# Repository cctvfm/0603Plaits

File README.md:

# 0603Plaits
a 603 Conversion of the Mutable Instruments Module Plaints
Confirmed working.
# TODO
Fix Eagle files. The .sch and .brd are inconsistent due to a crash after finalizing design

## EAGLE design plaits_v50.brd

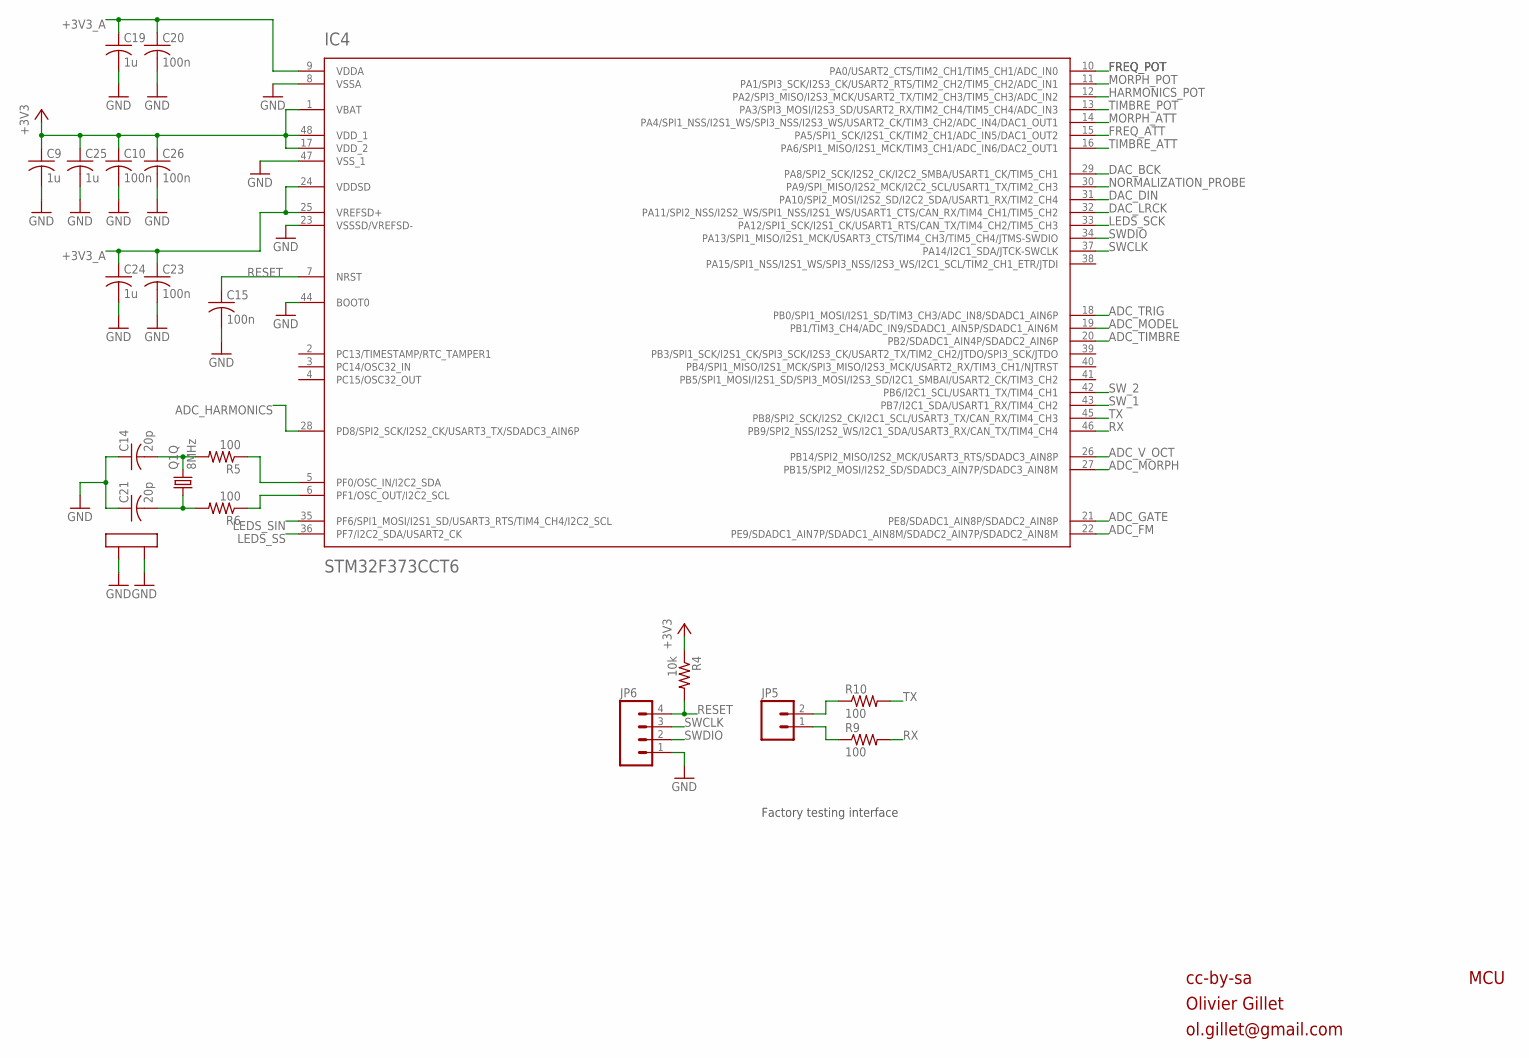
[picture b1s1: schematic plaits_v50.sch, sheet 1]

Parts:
C9, C19, C24, C25: 1u; C0603K
C10, C15, C20, C23, C26: 100n; C0603K
C14, C21: 20p; C0603K
IC4: STM32F373CCT6; LQFP48
JP5: M02PTH; 1X02
JP6: M04PTH; 1X04
Q1: 8MHz; CTS406
R4: 10k; R0603
R5, R6, R9, R10: 100; R0603

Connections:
+3V3: C9.1, C10.1, C25.1, C26.1, IC4.1 (VBAT), IC4.17 (VDD_2), IC4.48 (VDD_1), R4.1; also elsewhere on the board
+3V3_A: C19.1, C20.1, C23.1, C24.1, IC4.9 (VDDA), IC4.24 (VDDSD), IC4.25 (VREFSD+); also elsewhere on the board
ADC_FM: IC4.22 (PE9/SDADC1_AIN7P/SDADC1_AIN8M/SDADC2_AI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); also elsewhere on the board
ADC_GATE: IC4.21 (PE8/SDADC1_AIN8P/SDADC2_AIN8P); also elsewhere on the board
ADC_HARMONICS: IC4.28 (PD8/SPI2_SCK/I2S2_CK/USART3_TX/SDADC3_A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); also elsewhere on the board
ADC_MODEL: IC4.19 (PB1/TIM3_CH4/ADC_IN9/SDADC1_AIN5P/SDADC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); also elsewhere on the board
ADC_MORPH: IC4.27 (PB15/SPI2_MOSI/I2S2_SD/SDADC3_AIN7P/SDA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); also elsewhere on the board
ADC_TIMBRE: IC4.20 (PB2/SDADC1_AIN4P/SDADC2_AIN6P); also elsewhere on the board
ADC_TRIG: IC4.18 (PB0/SPI1_MOSI/I2S1_SD/TIM3_CH3/ADC_IN8/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); also elsewhere on the board
ADC_V_OCT: IC4.26 (PB14/SPI2_MISO/I2S2_MCK/USART3_RTS/SDAD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); also elsewhere on the board
DAC_BCK: IC4.29 (PA8/SPI2_SCK/I2S2_CK/I2C2_SMBA/USART1_C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); also elsewhere on the board
DAC_DIN: IC4.31 (PA10/SPI2_MOSI/I2S2_SD/I2C2_SDA/USART1_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); also elsewhere on the board
DAC_LRCK: IC4.32 (PA11/SPI2_NSS/I2S2_WS/SPI1_NSS/I2S1_WS/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); also elsewhere on the board
FREQ_ATT: IC4.15 (PA5/SPI1_SCK/I2S1_CK/TIM2_CH1/ADC_IN5/D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); also elsewhere on the board
FREQ_POT: IC4.10 (PA0/USART2_CTS/TIM2_CH1/TIM5_CH1/ADC_IN0); also elsewhere on the board
GND: C9.2, C10.2, C14.1, C15.2, C19.2, C20.2, C21.1, C23.2, C24.2, C25.2, C26.2, IC4.8 (VSSA), IC4.23 (VSSSD/VREFSD-), IC4.44 (BOOT0), IC4.47 (VSS_1), JP6.1, Q1.2 (LID1), Q1.4 (LID2); also elsewhere on the board
HARMONICS_POT: IC4.12 (PA2/SPI3_MISO/I2S3_MCK/USART2_TX/TIM2_C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); also elsewhere on the board
LEDS_SCK: IC4.33 (PA12/SPI1_SCK/I2S1_CK/USART1_RTS/CAN_TX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); also elsewhere on the board
LEDS_SIN: IC4.35 (PF6/SPI1_MOSI/I2S1_SD/USART3_RTS/TIM4_C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); also elsewhere on the board
LEDS_SS: IC4.36 (PF7/I2C2_SDA/USART2_CK); also elsewhere on the board
MORPH_ATT: IC4.14 (PA4/SPI1_NSS/I2S1_WS/SPI3_NSS/I2S3_WS/U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); also elsewhere on the board
MORPH_POT: IC4.11 (PA1/SPI3_SCK/I2S3_CK/USART2_RTS/TIM2_CH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); also elsewhere on the board
unnamed: IC4.5 (PF0/OSC_IN/I2C2_SDA), R5.1
unnamed: IC4.6 (PF1/OSC_OUT/I2C2_SCL), R6.1
unnamed: C14.2, Q1.3 (2), R5.2
unnamed: JP5.2, R10.1
unnamed: C21.2, Q1.1, R6.2
unnamed: JP5.1, R9.1
NORMALIZATION_PROBE: IC4.30 (PA9/SPI_MISO/I2S2_MCK/I2C2_SCL/USART1_T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); also elsewhere on the board
RESET: C15.1, IC4.7 (NRST), JP6.4, R4.2
RX: IC4.46 (PB9/SPI2_NSS/I2S2_WS/I2C1_SDA/USART3_RX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), R9.2
SWCLK: IC4.37 (PA14/I2C1_SDA/JTCK-SWCLK), JP6.3
SWDIO: IC4.34 (PA13/SPI1_MISO/I2S1_MCK/USART3_CTS/TIM4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), JP6.2
SW_1: IC4.43 (PB7/I2C1_SDA/USART1_RX/TIM4_CH2); also elsewhere on the board
SW_2: IC4.42 (PB6/I2C1_SCL/USART1_TX/TIM4_CH1); also elsewhere on the board
TIMBRE_ATT: IC4.16 (PA6/SPI1_MISO/I2S1_MCK/TIM3_CH1/ADC_IN6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); also elsewhere on the board
TIMBRE_POT: IC4.13 (PA3/SPI3_MOSI/I2S3_SD/USART2_RX/TIM2_CH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); also elsewhere on the board
TX: IC4.45 (PB8/SPI2_SCK/I2S2_CK/I2C1_SCL/USART3_TX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), R10.2

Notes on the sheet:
cc-by-sa
Olivier Gillet
ol.gillet@gmail.com
MCU
Factory testing interface

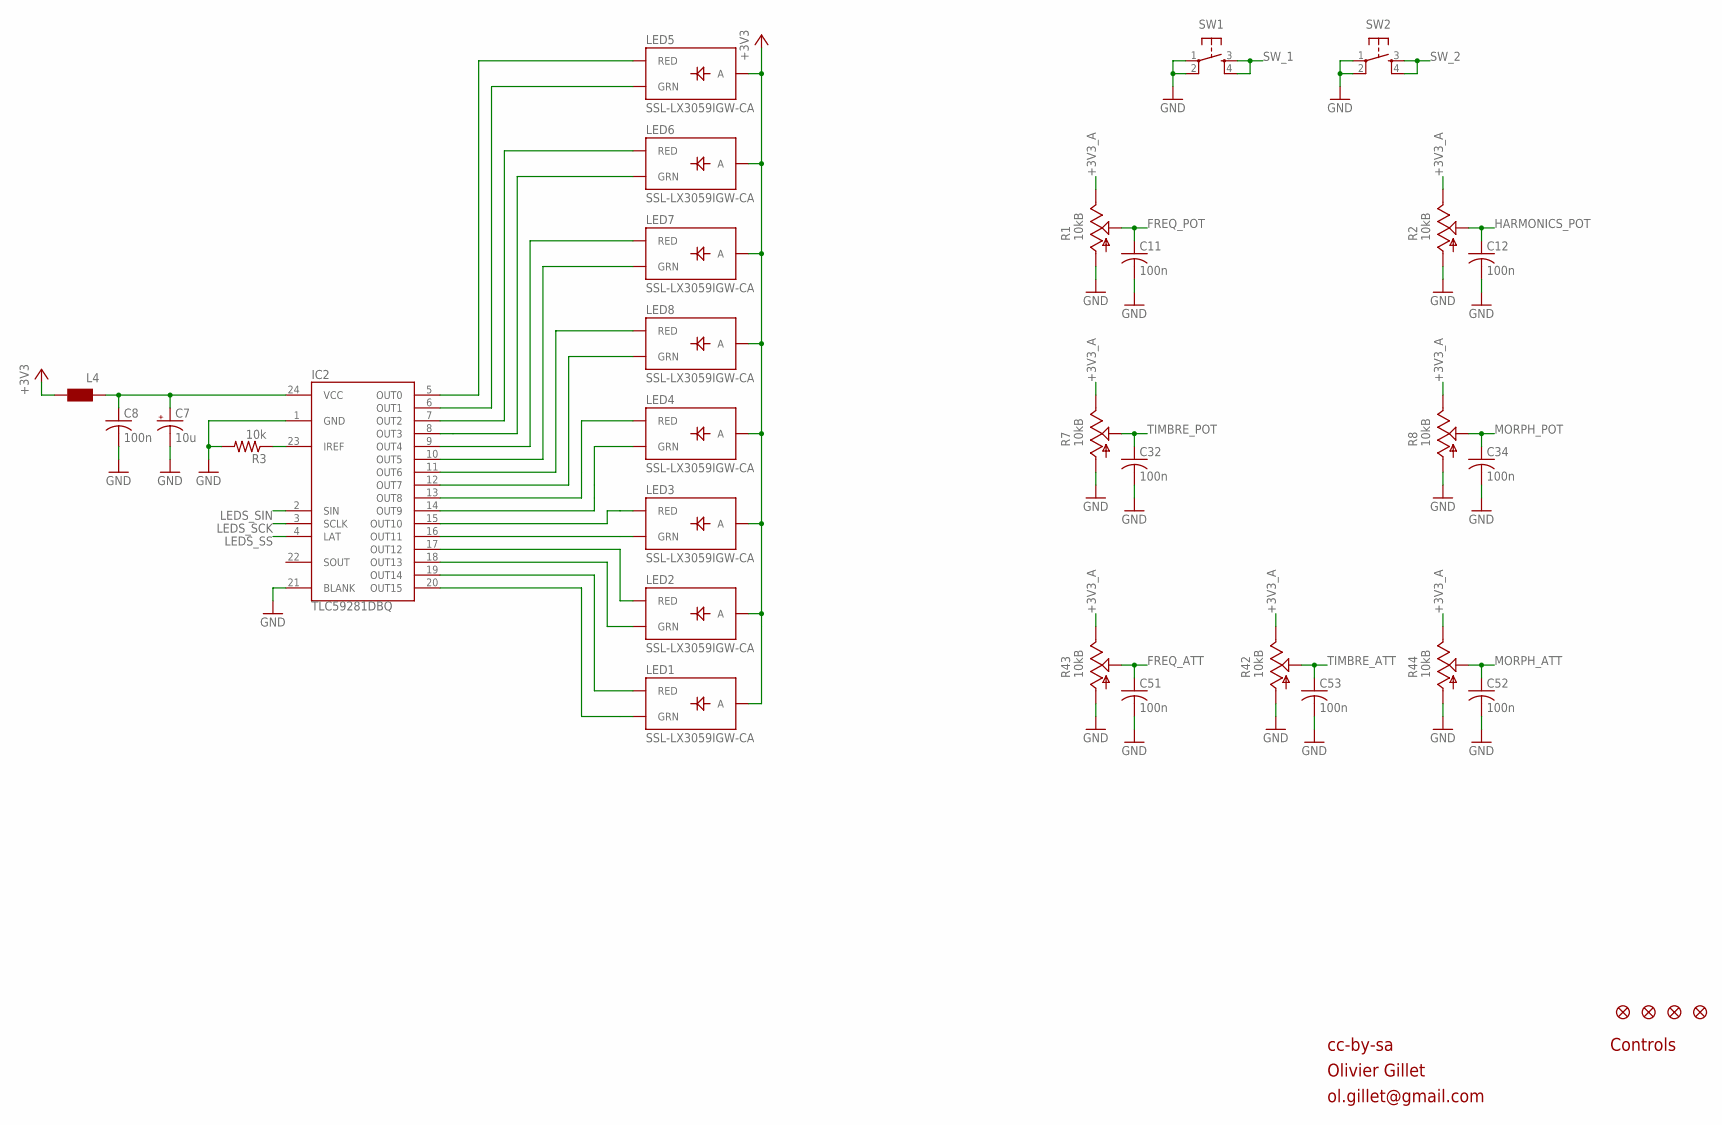
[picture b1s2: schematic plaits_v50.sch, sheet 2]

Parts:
C7: 10u; PANASONIC_A
C8, C11, C12, C32, C34, C51, C52, C53: 100n; C0603K
IC2: TLC59281DBQ; TSSOP24_0635
JP1, JP2, JP3, JP4: FIDUCIAL1X2; FIDUCIAL-1X2
L4: WE-CBF_0603; 0603
LED1, LED2, LED3, LED4, LED5, LED6, LED7, LED8: SSL-LX3059IGW-CA; LED-BICOLOR-THROUGHHOLE-LUMEX
R1, R2, R7, R8: 10kB; ALPS_POT_VERTICAL_PS
R3: 10k; R0603
R42, R43, R44: 10kB; ALPS_POT_VERTICAL
SW1, SW2: TAC_SWITCHPTH; TACTILE-PTH

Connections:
+3V3: L4.2, LED1.A, LED2.A, LED3.A, LED4.A, LED5.A, LED6.A, LED7.A, LED8.A; also elsewhere on the board
+3V3_A: R1.P$1 (E), R2.P$1 (E), R7.P$1 (E), R8.P$1 (E), R42.P$1 (E), R43.P$1 (E), R44.P$1 (E); also elsewhere on the board
FREQ_ATT: C51.1, R43.P$2 (S); also elsewhere on the board
FREQ_POT: C11.1, R1.P$2 (S); also elsewhere on the board
GND: C7.-, C8.2, C11.2, C12.2, C32.2, C34.2, C51.2, C52.2, C53.2, IC2.1 (GND), IC2.21 (BLANK), R1.P$3 (A), R2.P$3 (A), R3.2, R7.P$3 (A), R8.P$3 (A), R42.P$3 (A), R43.P$3 (A), R44.P$3 (A), SW1.1, SW1.2, SW2.1, SW2.2; also elsewhere on the board
HARMONICS_POT: C12.1, R2.P$2 (S); also elsewhere on the board
LEDS_SCK: IC2.3 (SCLK); also elsewhere on the board
LEDS_SIN: IC2.2 (SIN); also elsewhere on the board
LEDS_SS: IC2.4 (LAT); also elsewhere on the board
MORPH_ATT: C52.1, R44.P$2 (S); also elsewhere on the board
MORPH_POT: C34.1, R8.P$2 (S); also elsewhere on the board
unnamed: IC2.12 (OUT7), LED8.GREEN_C (GRN)
unnamed: IC2.11 (OUT6), LED8.RED_C (RED)
unnamed: IC2.10 (OUT5), LED7.GREEN_C (GRN)
unnamed: IC2.9 (OUT4), LED7.RED_C (RED)
unnamed: IC2.8 (OUT3), LED6.GREEN_C (GRN)
unnamed: IC2.13 (OUT8), LED4.RED_C (RED)
unnamed: IC2.7 (OUT2), LED6.RED_C (RED)
unnamed: IC2.14 (OUT9), LED4.GREEN_C (GRN)
unnamed: IC2.6 (OUT1), LED5.GREEN_C (GRN)
unnamed: IC2.15 (OUT10), LED3.RED_C (RED)
unnamed: IC2.16 (OUT11), LED3.GREEN_C (GRN)
unnamed: IC2.17 (OUT12), LED2.RED_C (RED)
unnamed: IC2.18 (OUT13), LED2.GREEN_C (GRN)
unnamed: IC2.19 (OUT14), LED1.RED_C (RED)
unnamed: IC2.5 (OUT0), LED5.RED_C (RED)
unnamed: IC2.20 (OUT15), LED1.GREEN_C (GRN)
unnamed: C7.+, C8.1, IC2.24 (VCC), L4.1
unnamed: IC2.23 (IREF), R3.1
SW_1: SW1.3, SW1.4; also elsewhere on the board
SW_2: SW2.3, SW2.4; also elsewhere on the board
TIMBRE_ATT: C53.1, R42.P$2 (S); also elsewhere on the board
TIMBRE_POT: C32.1, R7.P$2 (S); also elsewhere on the board

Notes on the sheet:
cc-by-sa
Olivier Gillet
ol.gillet@gmail.com
Controls

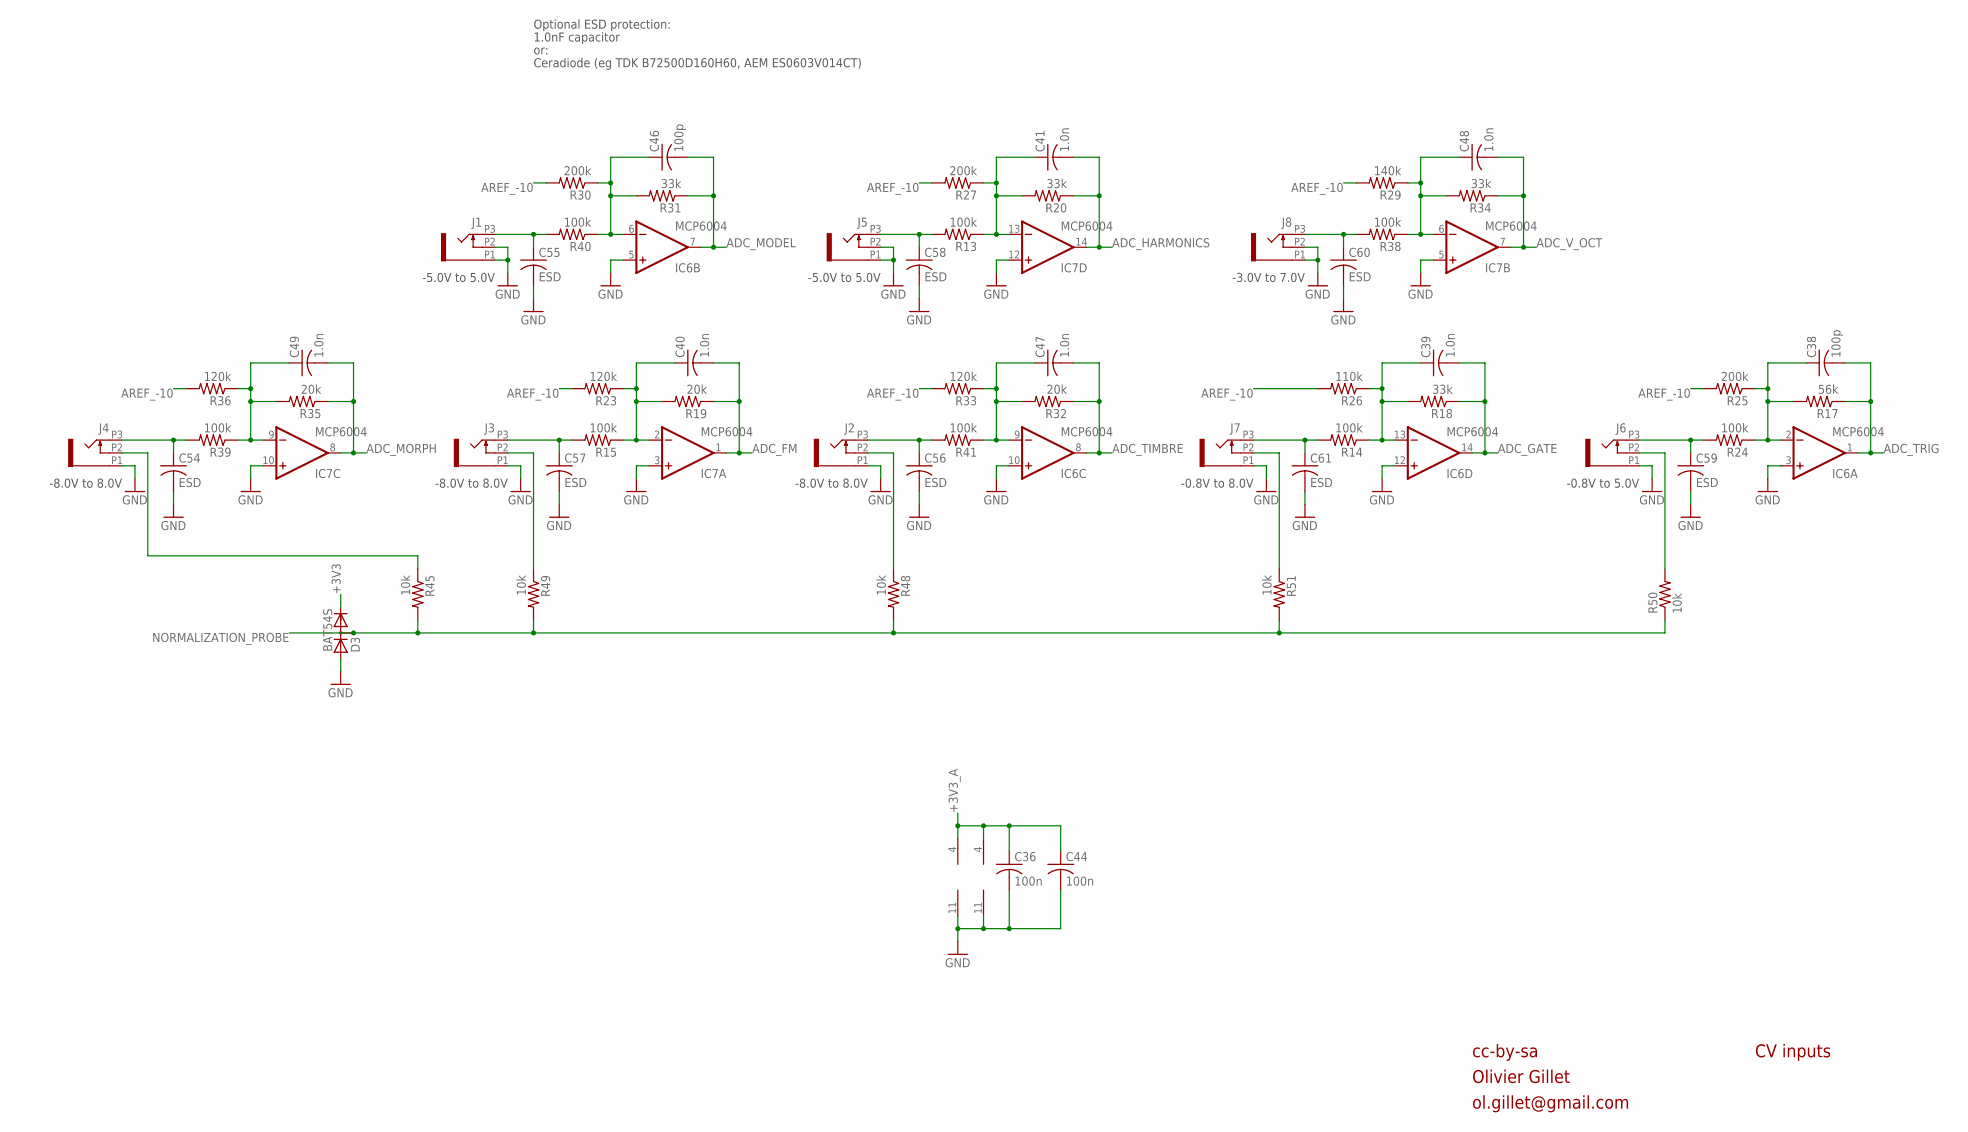
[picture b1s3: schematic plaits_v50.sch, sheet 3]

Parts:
C36, C44: 100n; C0603K
C38, C46: 100p; C0603K
C39, C40, C41, C47, C48, C49: 1.0n; C0603K
C54, C55, C57, C58, C59, C60, C61: ESD; C0603K
C56: ESD; C0603
D3: BAT54S; SOT23
IC6, IC7: MCP6004; TSSOP14_065
J1, J2, J3, J4, J5, J6, J7, J8: PJ301_THONKICONN6; WQP_PJ_301M6
R13, R14, R15, R24, R38, R39, R40, R41: 100k; R0603
R17: 56k; R0603
R18, R20, R31, R34: 33k; R0603
R19, R32, R35: 20k; R0603
R23, R33, R36: 120k; R0603
R25, R27, R30: 200k; R0603
R26: 110k; R0603
R29: 140k; R0603
R45, R48, R49, R50, R51: 10k; R0603

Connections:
+3V3: D3.2 (C); also elsewhere on the board
+3V3_A: C36.1, C44.1, IC6.4 (V+), IC7.4 (V+); also elsewhere on the board
ADC_FM: C40.2, IC7.1 (OUT), R19.1; also elsewhere on the board
ADC_GATE: C39.2, IC6.14 (OUT), R18.1; also elsewhere on the board
ADC_HARMONICS: C41.2, IC7.14 (OUT), R20.1; also elsewhere on the board
ADC_MODEL: C46.2, IC6.7 (OUT), R31.1; also elsewhere on the board
ADC_MORPH: C49.2, IC7.8 (OUT), R35.1; also elsewhere on the board
ADC_TIMBRE: C47.2, IC6.8 (OUT), R32.1; also elsewhere on the board
ADC_TRIG: C38.2, IC6.1 (OUT), R17.1; also elsewhere on the board
ADC_V_OCT: C48.2, IC7.7 (OUT), R34.1; also elsewhere on the board
AREF_-10: R23.2, R25.2, R26.2, R27.2, R29.2, R30.2, R33.2, R36.2; also elsewhere on the board
FM_IN: C57.1, J3.P3 (3), R15.2
GATE_IN: C61.1, J7.P3 (3), R14.2
GATE_IN1: C59.1, J6.P3 (3), R24.2
GND: C36.2, C44.2, C54.2, C55.2, C56.2, C57.2, C58.2, C59.2, C60.2, C61.2, D3.1 (A), IC6.3 (+IN), IC6.5 (+IN), IC6.10 (+IN), IC6.11 (V-), IC6.12 (+IN), IC7.3 (+IN), IC7.5 (+IN), IC7.10 (+IN), IC7.11 (V-), IC7.12 (+IN), J1.P1 (1), J1.P2 (2), J2.P1 (1), J3.P1 (1), J4.P1 (1), J5.P1 (1), J5.P2 (2), J6.P1 (1), J7.P1 (1), J8.P1 (1), J8.P2 (2); also elsewhere on the board
HARMONICS_IN: C58.1, J5.P3 (3), R13.2
MODEL_IN: C55.1, J1.P3 (3), R40.2
MORPH_IN: C54.1, J4.P3 (3), R39.2
unnamed: J6.P2 (2), R50.2
unnamed: C38.1, IC6.2 (-IN), R17.2, R24.1, R25.1
unnamed: J3.P2 (2), R49.1
unnamed: J2.P2 (2), R48.1
unnamed: J4.P2 (2), R45.1
unnamed: C39.1, IC6.13 (-IN), R14.1, R18.2, R26.1
unnamed: C48.1, IC7.6 (-IN), R29.1, R34.2, R38.1
unnamed: C56.1, J2.P3 (3), R41.2
unnamed: C49.1, IC7.9 (-IN), R35.2, R36.1, R39.1
unnamed: C40.1, IC7.2 (-IN), R15.1, R19.2, R23.1
unnamed: J7.P2 (2), R51.1
unnamed: C46.1, IC6.6 (-IN), R30.1, R31.2, R40.1
unnamed: C47.1, IC6.9 (-IN), R32.2, R33.1, R41.1
unnamed: C41.1, IC7.13 (-IN), R13.1, R20.2, R27.1
NORMALIZATION_PROBE: D3.3 (AC), R45.2, R48.2, R49.2, R50.1, R51.2; also elsewhere on the board
V_OCT_IN: C60.1, J8.P3 (3), R38.2

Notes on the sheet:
cc-by-sa
Olivier Gillet
ol.gillet@gmail.com
CV inputs
-3.0V to 7.0V
-8.0V to 8.0V
-5.0V to 5.0V
-0.8V to 8.0V
-0.8V to 5.0V
Optional ESD protection:
1.0nF capacitor
or:
Ceradiode (eg TDK B72500D160H60, AEM ES0603V014CT)

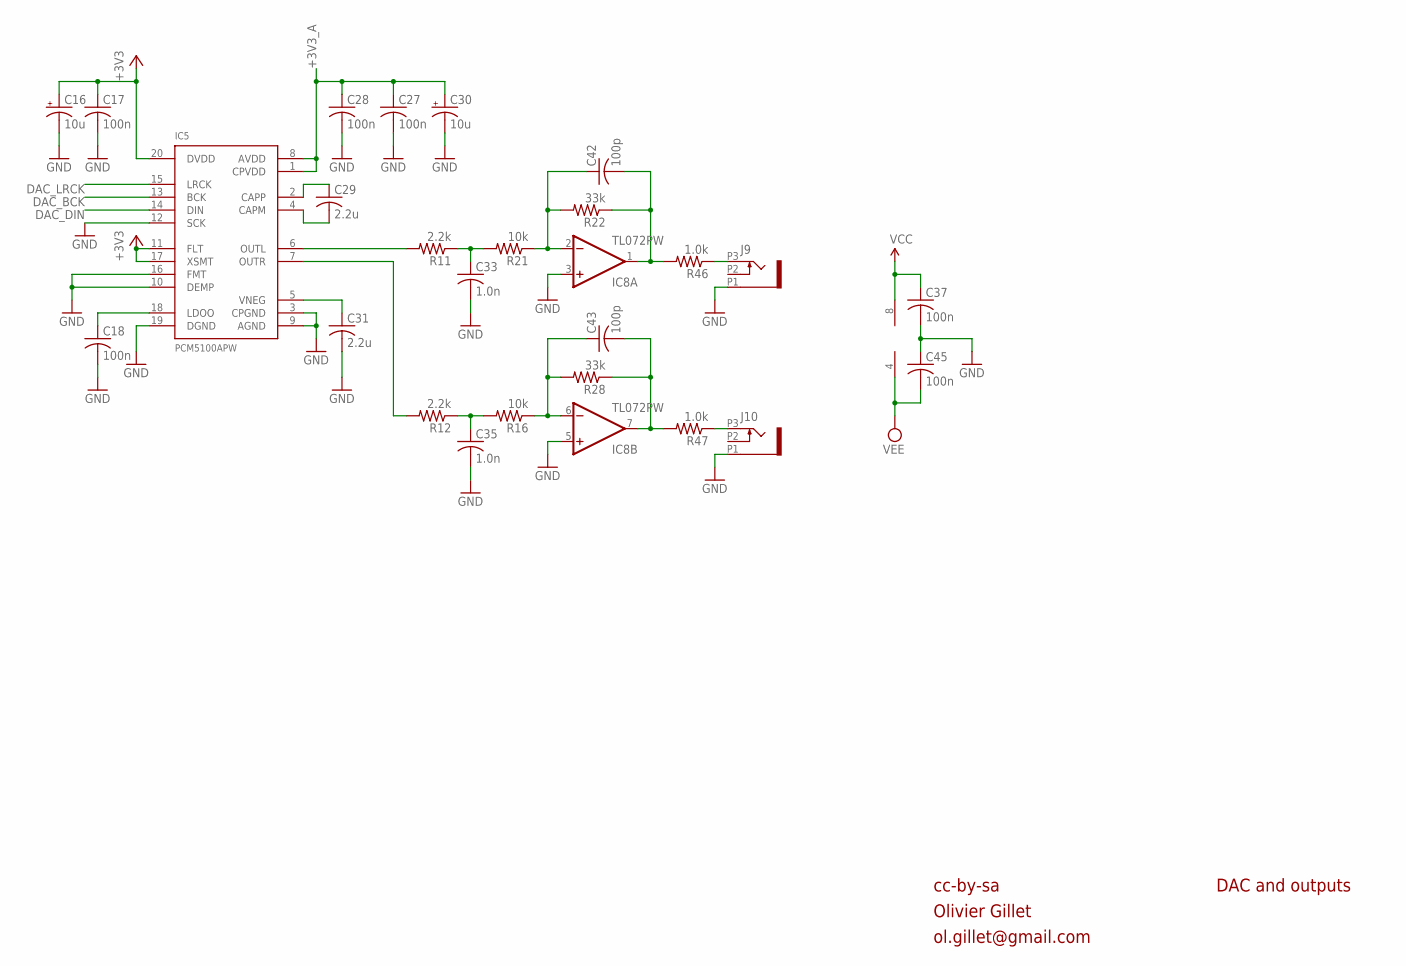
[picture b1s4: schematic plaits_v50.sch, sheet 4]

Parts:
C16, C30: 10u; PANASONIC_A
C17, C18, C27, C28, C37, C45: 100n; C0603K
C29, C31: 2.2u; C0805
C33, C35: 1.0n; C0603K
C42, C43: 100p; C0603K
IC5: PCM5100APW; SSOP20
IC8: TL072PW; TSSOP08
J9, J10: PJ301_THONKICONN6; WQP_PJ_301M6
R11, R12: 2.2k; R0603
R16, R21: 10k; R0603
R22, R28: 33k; R0603
R46, R47: 1.0k; R0603

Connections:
+3V3: C16.+, C17.1, IC5.11 (FLT), IC5.17 (XSMT), IC5.20 (DVDD); also elsewhere on the board
+3V3_A: C27.1, C28.1, C30.+, IC5.1 (CPVDD), IC5.8 (AVDD); also elsewhere on the board
DAC_BCK: IC5.13 (BCK); also elsewhere on the board
DAC_DIN: IC5.14 (DIN); also elsewhere on the board
DAC_LRCK: IC5.15 (LRCK); also elsewhere on the board
GND: C16.-, C17.2, C18.2, C27.2, C28.2, C30.-, C31.2, C33.2, C35.2, C37.2, C45.1, IC5.3 (CPGND), IC5.9 (AGND), IC5.10 (DEMP), IC5.12 (SCK), IC5.16 (FMT), IC5.19 (DGND), IC8.3 (+IN), IC8.5 (+IN), J9.P1 (1), J10.P1 (1); also elsewhere on the board
unnamed: C29.1, IC5.2 (CAPP)
unnamed: C29.2, IC5.4 (CAPM)
unnamed: IC5.6 (OUTL), R11.2
unnamed: C33.1, R11.1, R21.2
unnamed: C35.1, R12.1, R16.2
unnamed: C31.1, IC5.5 (VNEG)
unnamed: C18.1, IC5.18 (LDOO)
unnamed: IC5.7 (OUTR), R12.2
unnamed: C43.1, IC8.6 (-IN), R16.1, R28.2
unnamed: C43.2, IC8.7 (OUT), R28.1, R47.2
unnamed: C42.1, IC8.2 (-IN), R21.1, R22.2
unnamed: C42.2, IC8.1 (OUT), R22.1, R46.2
unnamed: J9.P3 (3), R46.1
unnamed: J10.P3 (3), R47.1
VCC: C37.1, IC8.8 (V+); also elsewhere on the board
VEE: C45.2, IC8.4 (V-); also elsewhere on the board

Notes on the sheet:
cc-by-sa
Olivier Gillet
ol.gillet@gmail.com
DAC and outputs

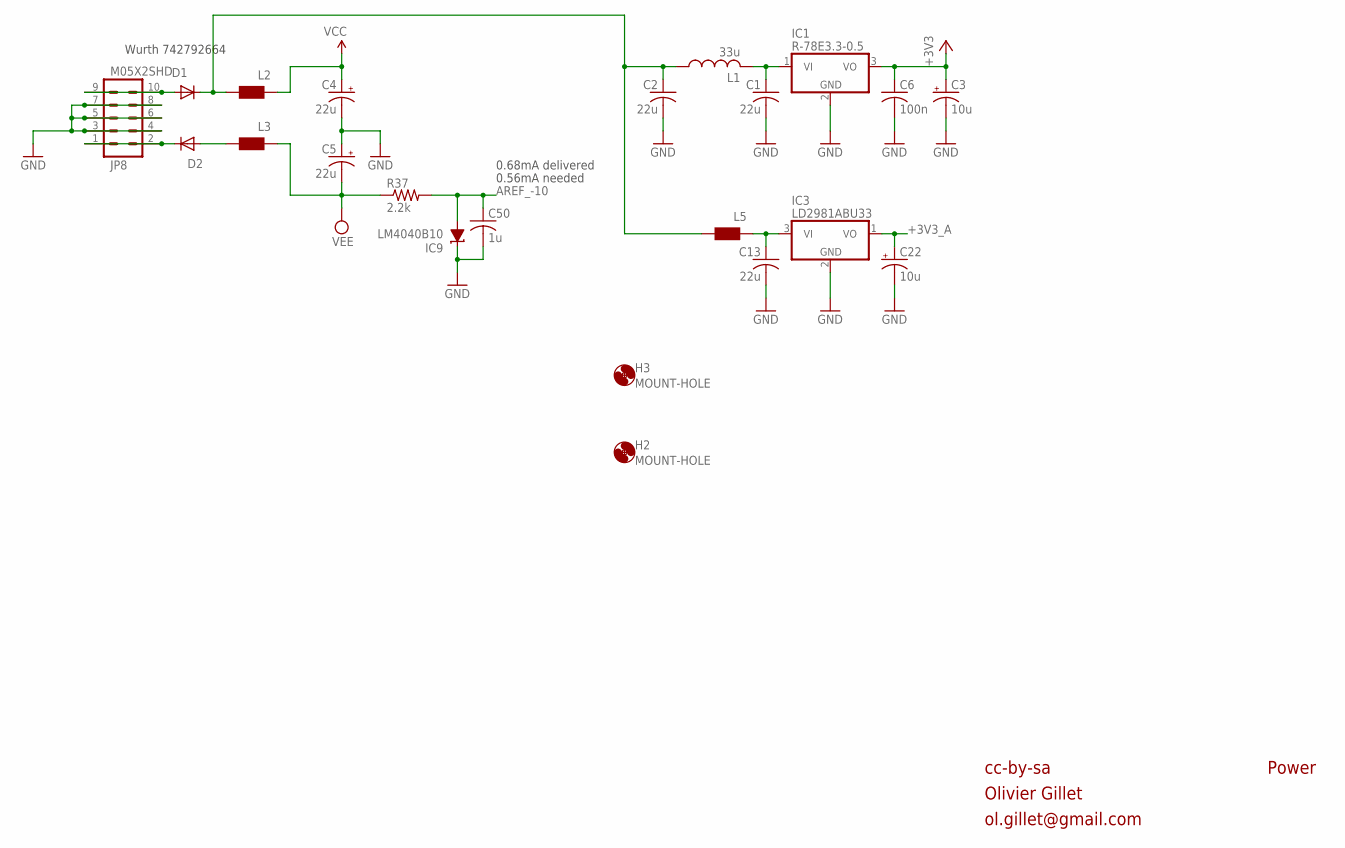
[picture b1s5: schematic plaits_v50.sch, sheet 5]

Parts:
C1, C2, C13: 22u; C1206
C3, C22: 10u; PANASONIC_A
C4, C5: 22u; PANASONIC_B
C6: 100n; C0603K
C50: 1u; C0603K
D1, D2: 1N5819HW; SOD123
H2, H3: MOUNT-HOLE; 3,0TINY
IC1: R-78E3.3-0.5; WE78
IC3: LD2981ABU33; SOT89
IC9: LM4040B10; DBZ_R-PDSO-G3
JP8: M05X2SHD; 2X5-SHROUDED
L1: 33u; L2012C
L2, L3, L5: WE-CBF_0603; 0603
R37: 2.2k; R0603

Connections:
+3V3: C3.+, C6.1, IC1.3 (VO); also elsewhere on the board
+3V3_A: C22.+, IC3.1 (VO); also elsewhere on the board
AREF_-10: C50.1, IC9.2 (A), R37.2; also elsewhere on the board
GND: C1.2, C2.2, C3.-, C4.-, C5.+, C6.2, C13.2, C22.-, C50.2, IC1.2 (GND), IC3.2 (GND), IC9.1 (C), JP8.3, JP8.4, JP8.5, JP8.6, JP8.7, JP8.8; also elsewhere on the board
unnamed: C1.1, IC1.1 (VI), L1.2
unnamed: D2.A, L3.2
unnamed: C2.1, D1.C, L1.1, L2.2, L5.2
unnamed: C13.1, IC3.3 (VI), L5.1
unnamed: D1.A, JP8.9, JP8.10
unnamed: D2.C, JP8.1, JP8.2
VCC: C4.+, L2.1; also elsewhere on the board
VEE: C5.-, L3.1, R37.1; also elsewhere on the board

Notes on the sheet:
cc-by-sa
Olivier Gillet
ol.gillet@gmail.com
Power
0.56mA needed
Wurth 742792664
0.68mA delivered

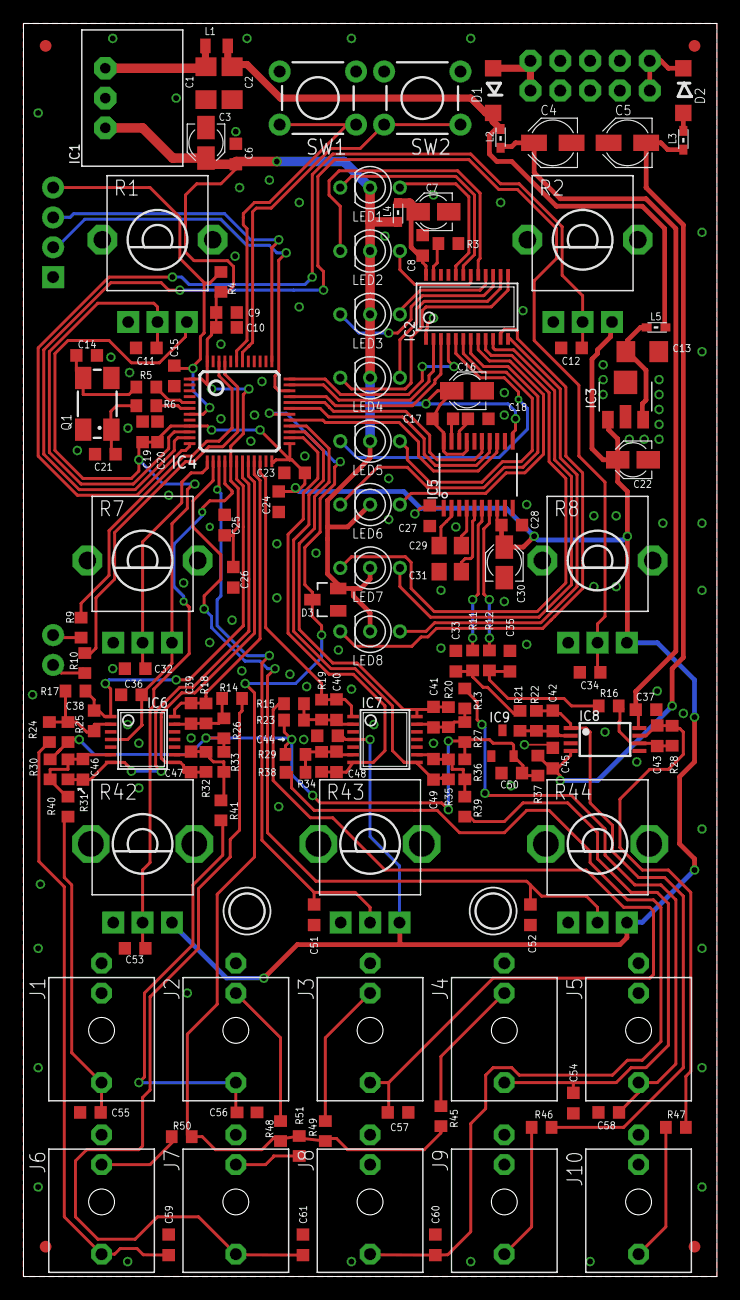
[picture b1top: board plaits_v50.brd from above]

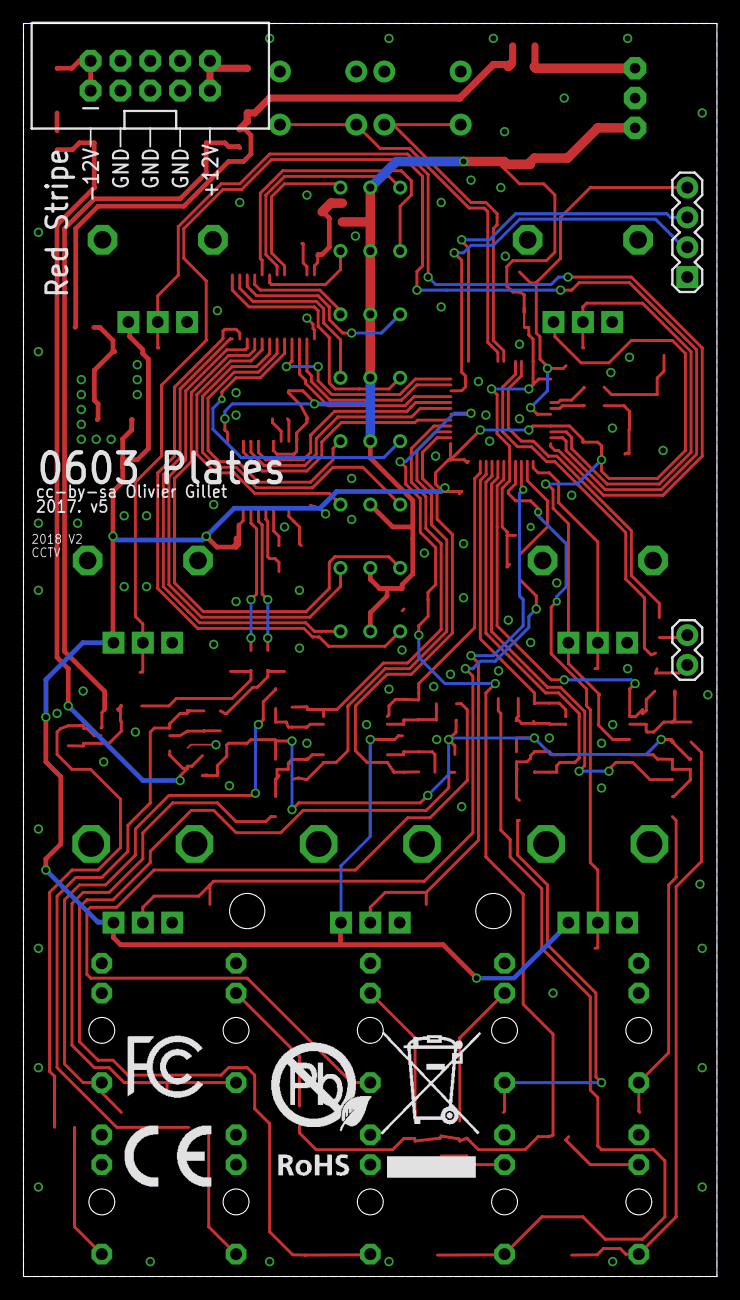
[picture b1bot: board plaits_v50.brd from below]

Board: 2 copper layers, 59.0 x 106.7 mm, 162 parts (6 on the bottom side), 100 nets.

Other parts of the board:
U$1: FCC_MEDIUM
U$2: ROHS_BIG
U$3: CE_MEDIUM

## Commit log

2018-09-19 Initial Upload
2018-09-19 Fixed placement of passives
    Some resistors were "on top" of pots, moved them out of the way
2018-09-19 Fixed tname positioning
2018-09-19 Fixed more Attribute placement
2018-09-20 Fixed potential clearance issues
2018-11-02 Changed name to Plates, fixed spelling error
